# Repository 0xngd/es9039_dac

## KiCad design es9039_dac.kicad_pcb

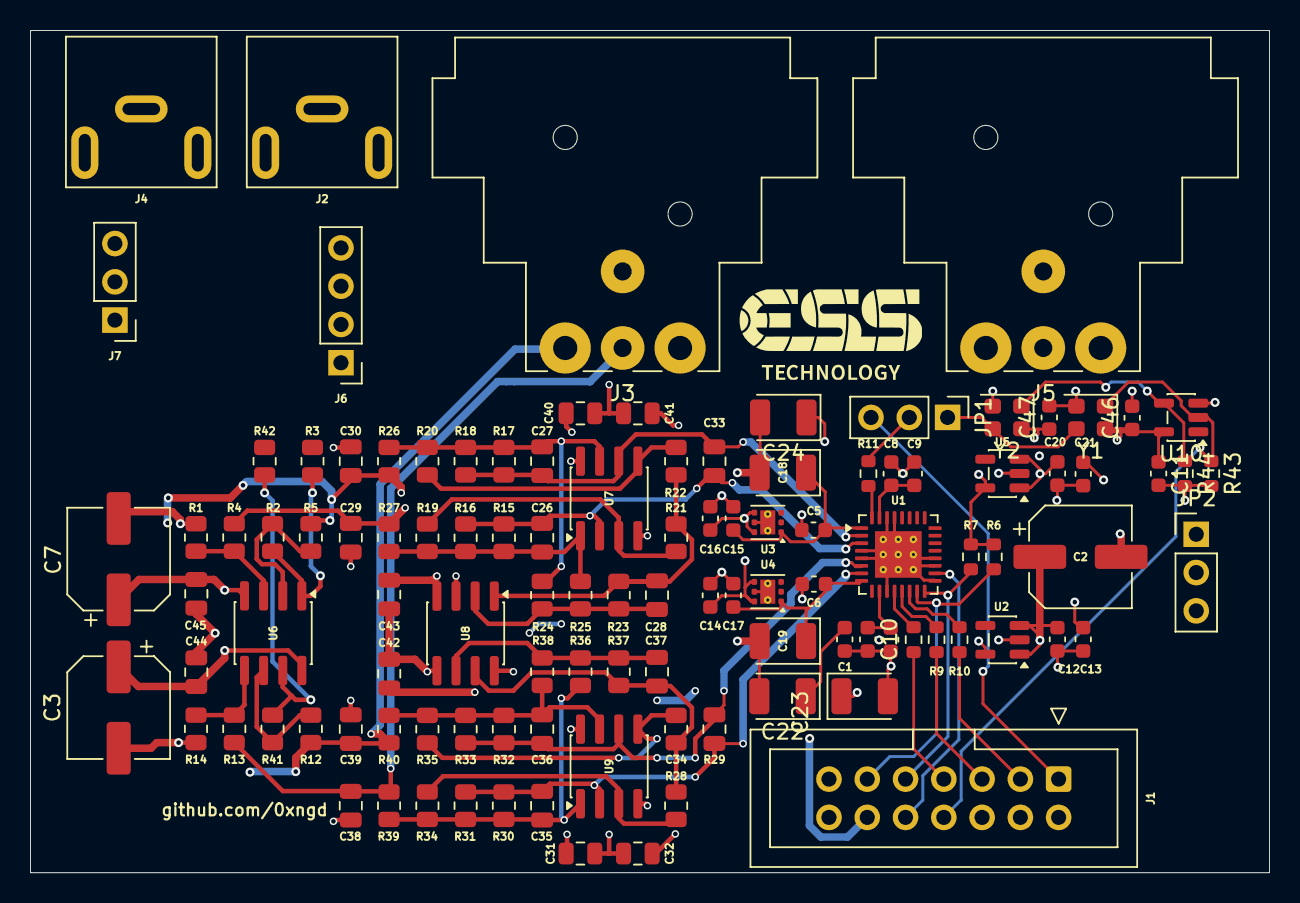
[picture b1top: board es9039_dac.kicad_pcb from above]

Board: 4 copper layers, 82.2 x 55.9 mm, 111 parts (0 on the bottom side), 53 nets.

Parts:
C1, C4, C5, C6, C8, C11, C46, C47: 100n; C_0603_1608Metric
C2, C3, C7: 100u; CP_Elec_6.3x5.8
C9, C12, C13, C20, C21: 4u7; C_0603_1608Metric
C10: 10u; C_0603_1608Metric
C14, C15, C16, C17: 1u; C_0603_1608Metric
C18, C19, C22, C23, C24: 47u; CP_EIA-3528-12_Kemet-T
C26, C27, C35, C36: 510p; C_0805_2012Metric
C28, C37: 51p; C_0805_2012Metric
C29, C30, C33, C34, C38, C39: 2n2; C_0805_2012Metric
C31, C32, C40, C41, C42, C43, C44, C45: 470n; C_0805_2012Metric
J1: Conn_02x07_Odd_Even; IDC-Header_2x07_P2.54mm_Vertical
J2: RCA_L; RCA-105A
J3: XLR_R; Jack_XLR_Neutrik_NC3MAH-0_Horizontal
J4: RCA_R; RCA-105A
J5: XLR_L; Jack_XLR_Neutrik_NC3MAH-0_Horizontal
J6: BAL_OUT; PinHeader_1x04_P2.54mm_Vertical
J7: UNBAL_OUT; PinHeader_1x03_P2.54mm_Vertical
JP1: MCLK_JUMPER; PinHeader_1x03_P2.54mm_Vertical
JP2: MCLK_JUMPER_PWR; PinHeader_1x03_P2.54mm_Vertical
R1, R2, R4, R5, R12, R13, R14, R24, R25, R37, R38, R41: 10K; R_0805_2012Metric
R3, R42: 100R; R_0805_2012Metric
R6, R7, R43, R44: 10K; R_0603_1608Metric
R8, R9, R10, R11: 22R; R_0603_1608Metric
R15, R16, R17, R18, R30, R31, R32, R33: 1K8; R_0805_2012Metric
R19, R20, R34, R35: 3K2; R_0805_2012Metric
R21, R22, R28, R29: 4R3; R_0805_2012Metric
R23, R36: 1M2; R_0805_2012Metric
R26, R27, R39, R40: 140; R_0805_2012Metric
U1: ES9039Q2M; QFN-32-1EP_5x5mm_P0.5mm_EP3.1x3.1mm_ThermalVias
U2, U5: TPS7A2033DBV; SOT-23-5
U3, U4: LP5912-3.3DRV; WSON-6-1EP_2x2mm_P0.65mm_EP1x1.6mm_ThermalVias
U6, U7, U8, U9: OPA1612AxD; SOIC-8_3.9x4.9mm_P1.27mm
U10: SN74LVC1G14DBV; SOT-23-5
Y1, Y2: 45.1584MHz; Oscillator_SMD_SiT_PQFN-4Pin_2.5x2.0mm

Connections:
+3.3V: C8.1, C9.1, C21.1, C24.1, JP2.2 (C), R6.2, R7.2, U1.31 (VCCA), U5.5 (OUT)
+3.3VA: C4.1, C10.1, C13.1, C23.1, U1.10 (AVDD), U2.5 (OUT)
+3.3VAL: C5.1, C15.1, C18.1, U1.1 (AVCC_DAC1), U3.1 (OUT)
+3.3VAR: C6.1, C17.1, C19.1, U1.8 (AVCC_DAC2), U4.1 (OUT)
+3.3VCLK: C11.1, C46.1, C47.1, JP2.1 (A), U10.5 (VCC), Y1.4 (Vdd), Y2.4 (Vdd)
+5V: C2.1, C12.1, C14.1, C16.1, C20.1, J1.12, U2.1 (IN), U2.3 (EN), U3.4 (EN), U3.6 (IN), U4.4 (EN), U4.6 (IN), U5.1 (IN), U5.3 (EN)
+12V: C3.1, C31.2, C40.2, C42.2, C44.2, J1.13, U6.8 (V+), U7.8 (V+), U8.8 (V+), U9.8 (V+)
-12V: C7.1, C32.2, C41.2, C43.2, C45.2, J1.14, U6.4 (V-), U7.4 (V-), U8.4 (V-), U9.4 (V-)
/AMANERO_MCLK: J1.1, JP1.3 (B)
/CRYSTAL_MCLK: JP1.1 (A), Y1.3 (OUT), Y2.3 (OUT)
/DAC_MCLK: JP1.2 (C), R11.1
/DAC_STBY: J1.10, U1.18 (CHIP_EN)
/FREQ_SEL: J1.8, R43.1, U10.2, Y1.1 (OE)
/I2C_SCL: J1.11, R6.1, U1.15 (SCLK/SCL/HW1)
/I2C_SDA: J1.9, R7.1, U1.16 (MOSI/SDA/HW0)
/I2S_BCLK: J1.7, R8.2
/I2S_DATA: J1.3, R10.2
/I2S_LRCK: J1.5, R9.2
DAC1: C26.1, C33.1, R15.1, R16.1, U1.3 (DAC1), U7.2 (-)
DAC1B: C27.1, C33.2, R17.1, R18.1, U1.2 (DAC1B), U7.6 (-)
DAC2: C34.1, C35.1, R30.1, R31.1, U1.7 (DAC2), U9.2 (-)
DAC2B: C34.2, C36.1, R32.1, R33.1, U1.6 (DAC2B), U9.6 (-)
GNDA: C1.2, C2.2, C3.2, C4.2, C5.2, C6.2, C7.2, C8.2, C9.2, C10.2, C11.2, C12.2, C13.2, C14.2, C15.2, C16.2, C17.2, C18.2, C19.2, C20.2, C21.2, C22.2, C23.2, C24.2, C29.2, C30.2, C31.1, C32.1, C38.2, C39.2, C40.1, C41.1, C42.1, C43.1, C44.1, C45.1, C46.2, C47.2, J1.2, J1.4, J1.6, J2.2 (Ext), J3.1, J3.G, J4.2 (Ext), J5.1, J5.G, J7.1, R1.2, R14.2, R43.2, R44.2, U1.4 (AGND_DAC1), U1.5 (AGND_DAC2), U1.11 (GND), U1.17 (RT1), U1.19 (SS/ADDR1/HW2), U1.20 (MISO/ADDR0/MUTE_CTRL), U1.29 (MODE), U1.30 (GND), U1.33 (EP), U2.2 (GND), U3.5 (GND), U3.7 (EP), U4.5 (GND), U4.7 (EP), U5.2 (GND), U8.3 (+), U8.5 (+), U10.3 (GND), Y1.2 (GND), Y2.2 (GND)
unnamed: C26.2, R15.2, R16.2, R19.2, R24.2, R27.2, U7.1
unnamed: C27.2, R17.2, R18.2, R20.2, R25.1, R26.2, U7.7
unnamed: C28.1, R21.1, R22.2, R23.1, U8.1
unnamed: C35.2, R30.2, R31.2, R34.2, R37.2, R39.2, U9.1
unnamed: C36.2, R32.2, R33.2, R35.2, R38.1, R40.2, U9.7
unnamed: C37.1, R28.1, R29.2, R36.1, U8.7
unnamed: R2.2, R3.1, U6.1
unnamed: R41.2, R42.1, U6.7
unnamed: R9.1, U1.13 (DATA1)
unnamed: R10.1, U1.14 (DATA2)
unnamed: R8.1, U1.12 (DATA_CLK)
unnamed: C1.1, C22.1, U1.9 (DVDD)
unnamed: R11.2, U1.32 (MCLK)
unnamed: R1.1, R4.2, U6.3 (+)
unnamed: R2.1, R5.2, U6.2 (-)
unnamed: R13.2, R14.1, U6.5 (+)
unnamed: R12.2, R41.1, U6.6 (-)
unnamed: R19.1, R21.2, U7.3 (+)
unnamed: R20.1, R22.1, U7.5 (+)
unnamed: C28.2, R23.2, R24.1, R25.2, U8.2 (-)
unnamed: C37.2, R36.2, R37.1, R38.2, U8.6 (-)
unnamed: R28.2, R34.1, U9.3 (+)
unnamed: R29.1, R35.1, U9.5 (+)
unnamed: R44.1, U10.4, Y2.1 (OE)
OUT_L: C29.1, J5.3, J6.4, R4.1, R27.1
OUT_Lb: C30.1, J5.2, J6.3, R5.1, R26.1
OUT_R: C38.1, J3.3, J6.2, R13.1, R39.1
OUT_Rb: C39.1, J3.2, J6.1, R12.1, R40.1
UNBAL_OUT_L: J2.1 (In), J7.3, R3.2
UNBAL_OUT_R: J4.1 (In), J7.2, R42.2

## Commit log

2026-06-23 add libs
2026-06-23 some changes
2026-06-23 deleted pcb and some changes in schematic
2026-06-28 trace dac chip and add output stage
2026-06-29 traced o/s
2026-06-29 add rca
2026-06-29 almost ready
2026-06-30 add oscillator
